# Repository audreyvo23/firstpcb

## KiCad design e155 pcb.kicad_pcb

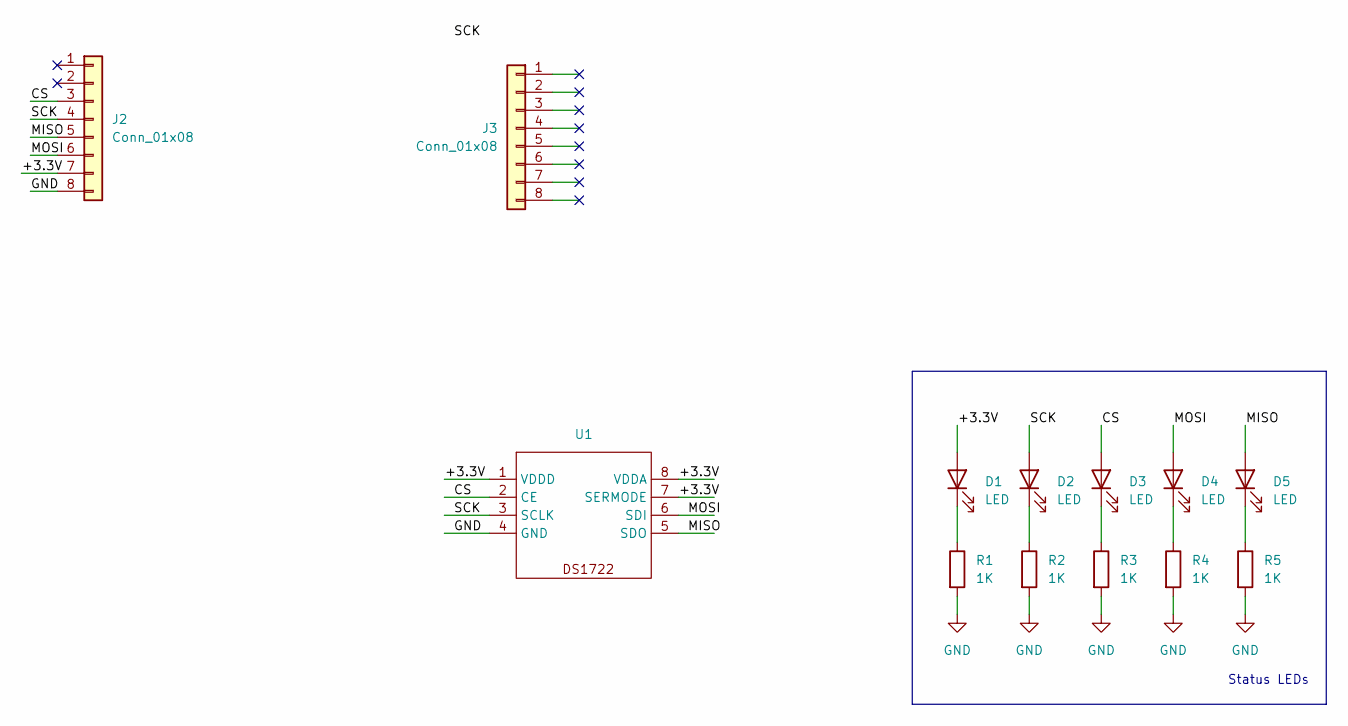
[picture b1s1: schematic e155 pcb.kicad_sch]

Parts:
D1, D2, D3, D4, D5: LED; LED_0805_2012Metric
J1: Conn_01x08_Pin
J2, J3: Conn_01x08; PinHeader_1x08_P2.54mm_Vertical
R1, R2, R3, R4, R5: 1K; R_0805_2012Metric
U1: SOIC-8_3.9x4.9mm_P1.27mm

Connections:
/+3.3V: D1.2 (A), J2.7, U1.1 (VDDD), U1.7 (SERMODE), U1.8 (VDDA)
/CS: D3.2 (A), J2.3, U1.2 (CE)
/MISO: D5.2 (A), J2.5, U1.5 (SDO)
/MOSI: D4.2 (A), J2.6, U1.6 (SDI)
/SCK: D2.2 (A), J2.4, U1.3 (SCLK)
GND: J2.8, R1.2, R2.2, R3.2, R4.2, R5.2, U1.4 (GND)
unnamed: D1.1 (K), R1.1
unnamed: D2.1 (K), R2.1
unnamed: D3.1 (K), R3.1
unnamed: D4.1 (K), R4.1
unnamed: D5.1 (K), R5.1

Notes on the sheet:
Status LEDs

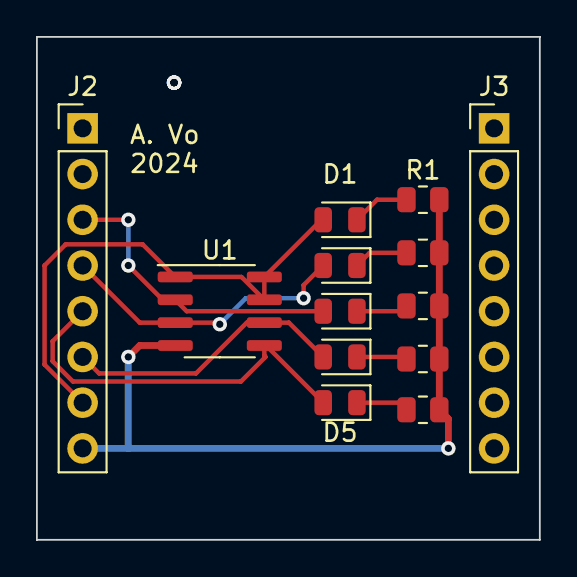
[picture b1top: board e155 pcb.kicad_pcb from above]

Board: 2 copper layers, 27.9 x 27.9 mm, 13 parts (0 on the bottom side), 11 nets.
